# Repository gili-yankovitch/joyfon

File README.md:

# Joyfon

A USB HID game controller for the Raspberry Pi Pico (RP2040).

Joyfon enumerates as a **standard USB HID gamepad**, so phones (Android), PCs,
and emulators recognize it with no driver or app. The button layout mimics a
Game Boy Color: a 4-way D-pad plus `A`, `B`, `X`, `Y`, shoulder buttons
(`SR`/`SL`), and `START` / `SELECT`.

## Enclosure & PCB

The 3D-printable enclosure is modeled in Onshape:
[Joyfon case (Onshape)](https://cad.onshape.com/documents/5b058211584da6ba94a5f3a2/w/7946df008143afeea2af8019/e/bb1aadbdb91d94f271c1447f?page=2&email=giliy%40nyxsecurity.net&renderMode=0&uiState=6a5551800e11d12ad61d855e).

| Case front | Case back |
| ---------- | --------- |
|  |  |

| PCB front | PCB back |
| --------- | -------- |
|  |  |

## Wiring

All buttons are **active-low**: wire each button between its GPIO and `GND`.
The firmware enables the RP2040's internal pull-ups, so external pull-up
resistors are optional (the description below assumes you already have them).

| Function        | GPIO  |
| --------------- | ----- |
| D-pad DOWN      | 0     |
| D-pad RIGHT     | 1     |
| D-pad UP        | 2     |
| D-pad LEFT      | 3     |
| B               | 4     |
| A               | 5     |
| X               | 20    |
| Y               | 21    |
| SR (R shoulder) | 22    |
| SL (L shoulder) | 25    |
| START           | 23    |
| SELECT          | 24    |
| Status LED      | 8     |

The status LED (GPIO8, active-high through a current-limiting resistor):

- **Blinks @ 250 ms** — USB not mounted (waiting for host).
- **Blinks @ 1 s** — USB suspended.
- **Solid while pressed** — mounted and running; lights up whenever any button
  is held, as live input feedback.

## HID mapping

The gamepad report is the TinyUSB standard gamepad (`hid_gamepad_report_t`):

| Physical button | HID control                        |
| --------------- | ---------------------------------- |
| D-pad           | Hat switch (8 directions)          |
| A               | Button 1 (`GAMEPAD_BUTTON_A`)      |
| B               | Button 2 (`GAMEPAD_BUTTON_B`)      |
| X               | Button 4 (`GAMEPAD_BUTTON_X`)      |
| Y               | Button 5 (`GAMEPAD_BUTTON_Y`)      |
| SR (R shoulder) | Button 8 (`GAMEPAD_BUTTON_TR`)     |
| SL (L shoulder) | Button 7 (`GAMEPAD_BUTTON_TL`)     |
| START           | Button 12 (`GAMEPAD_BUTTON_START`) |
| SELECT          | Button 11 (`GAMEPAD_BUTTON_SELECT`)|

Opposing D-pad directions cancel out (e.g. pressing UP and DOWN together
reports centered) so no impossible diagonal is ever sent. Reports are only sent
when the button state changes, keeping latency low and the bus quiet.

## Building

This project expects the [pico-sdk](https://github.com/raspberrypi/pico-sdk).
By default `CMakeLists.txt` looks for it at `../pico-sdk` (a sibling of this
folder). You can override that with the `PICO_SDK_PATH` environment variable.

Prerequisites: `cmake` (>= 3.13), the `arm-none-eabi` GCC toolchain, and the
SDK submodules (TinyUSB) initialized.

```bash
# from the joyfon/ directory
mkdir build && cd build
cmake ..                    # or: cmake -DPICO_SDK_PATH=/path/to/pico-sdk ..
make -j
```

The build produces `build/joyfon.uf2`.

## Flashing

1. Hold the **BOOTSEL** button while plugging the Pico into USB; it mounts as a
   mass-storage drive (`RPI-RP2`).
2. Copy `joyfon.uf2` onto it. The Pico reboots and re-enumerates as the
   "Joyfon Game Controller" gamepad.

After flashing, plug the Pico into a phone (via USB-OTG / USB-C). It should
appear as a connected gamepad, ready for use with emulators or any app that
supports HID controllers.

## Notes

- Uses the test VID `0xCafe` / PID `0x4007`. Use a VID/PID you own before
  distributing hardware.
- The RP2040 USB enumeration errata fix (RP2040-E5) is enabled in
  `CMakeLists.txt`; it reserves GPIO15 internally on RP2040 boards.

## Assembly guide

Open [the illustrated assembly guide](assembly.html) for the complete build sequence,
component inventory, fastener assignments and checks. All 35 assembly photos are
included locally in `images/assembly/`. The page shares the home page styling.

The `stl/` directory contains the 16 production STL parts, including the hinge
height extender and the updated USB holder and cover.

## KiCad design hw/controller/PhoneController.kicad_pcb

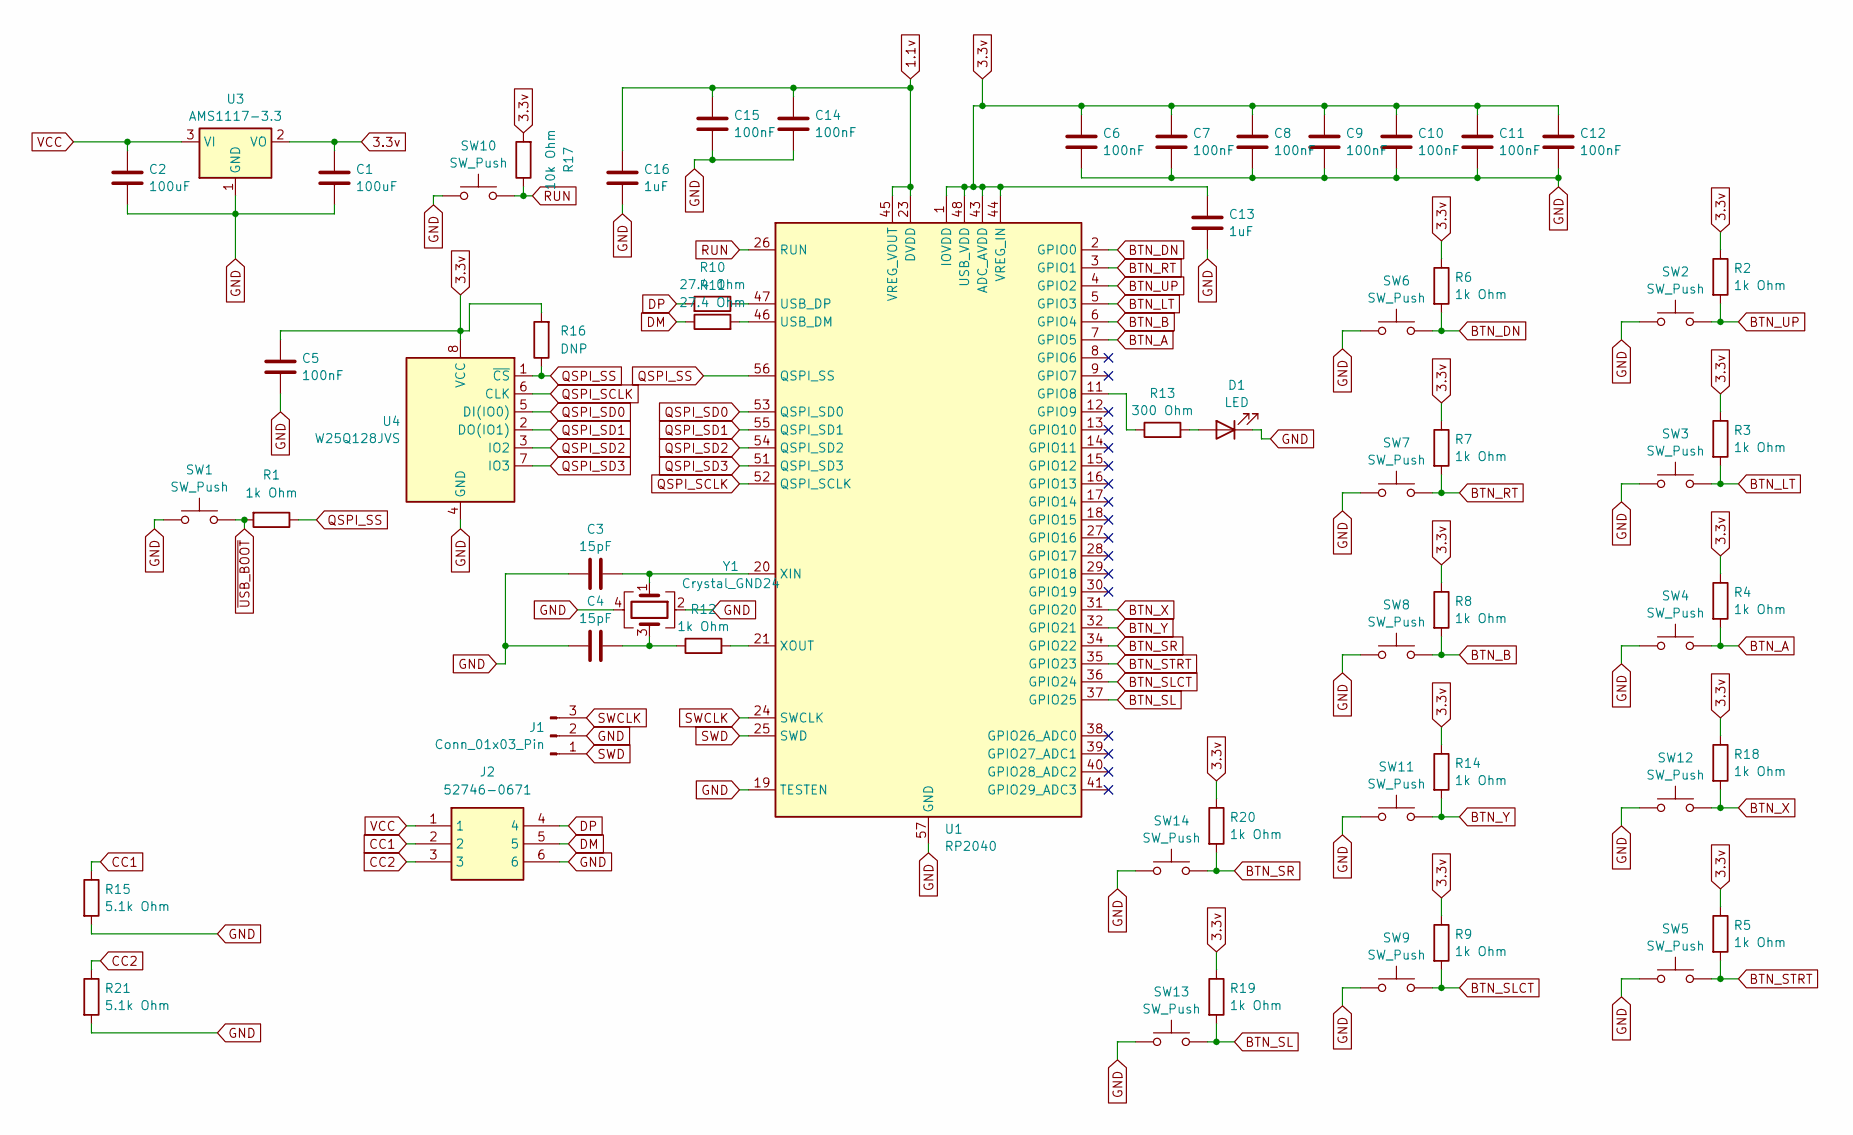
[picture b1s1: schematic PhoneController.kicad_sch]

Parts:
C1, C2: 100uF; C_1206_3216Metric_Pad1.33x1.80mm_HandSolder
C3, C4: 15pF; C_0805_2012Metric_Pad1.18x1.45mm_HandSolder
C5, C6, C7, C8, C9, C10, C11, C12, C14, C15: 100nF; C_0805_2012Metric_Pad1.18x1.45mm_HandSolder
C13, C16: 1uF; C_0805_2012Metric_Pad1.18x1.45mm_HandSolder
D1: LED; LED_0805_2012Metric_Pad1.15x1.40mm_HandSolder
J1: Conn_01x03_Pin; PinSocket_1x03_P2.54mm_Vertical
J2: 52746-0671; Mouser Part Number 538-52746-0671
R1, R2, R3, R4, R5, R6, R7, R8, R9, R12, R14, R18, R19, R20: 1k Ohm; R_0805_2012Metric_Pad1.20x1.40mm_HandSolder
R10, R11: 27.4 Ohm; R_0805_2012Metric_Pad1.20x1.40mm_HandSolder
R13: 300 Ohm; R_0805_2012Metric_Pad1.20x1.40mm_HandSolder
R15, R21: 5.1k Ohm; R_0805_2012Metric_Pad1.20x1.40mm_HandSolder
R16: DNP; R_0805_2012Metric_Pad1.20x1.40mm_HandSolder
R17: 10k Ohm; R_0805_2012Metric_Pad1.20x1.40mm_HandSolder
SW1, SW2, SW3, SW4, SW5, SW6, SW7, SW8, SW9, SW10, SW11, SW12, SW13, SW14: SW_Push; TS-1088-AR02016
U1: RP2040; QFN-56-1EP_7x7mm_P0.4mm_EP3.2x3.2mm
U3: AMS1117-3.3; SOT-223-3_TabPin2
U4: W25Q128JVS; SOIC127P790X216-8N
Y1: Crystal_GND24; Crystal_SMD_Abracon_ABM8G-4Pin_3.2x2.5mm

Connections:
1.1v: C14.2, C15.2, C16.2, U1.23 (DVDD), U1.45 (VREG_VOUT), U1.50 (DVDD)
3.3v: C1.1, C5.2, C6.2, C7.2, C8.2, C9.2, C10.2, C11.2, C12.2, C13.2, R2.1, R3.1, R4.1, R5.1, R6.1, R7.1, R8.1, R9.1, R14.1, R16.2, R17.2, R18.1, R19.1, R20.1, U1.1 (IOVDD), U1.10 (IOVDD), U1.22 (IOVDD), U1.33 (IOVDD), U1.42 (IOVDD), U1.43 (ADC_AVDD), U1.44 (VREG_IN), U1.48 (USB_VDD), U1.49 (IOVDD), U3.2 (VO), U4.8 (VCC)
BTN_A: R4.2, SW4.2, U1.7 (GPIO5)
BTN_B: R8.2, SW8.2, U1.6 (GPIO4)
BTN_DN: R6.2, SW6.2, U1.2 (GPIO0)
BTN_LT: R3.2, SW3.2, U1.5 (GPIO3)
BTN_RT: R7.2, SW7.2, U1.3 (GPIO1)
BTN_SL: R19.2, SW13.2, U1.37 (GPIO25)
BTN_SLCT: R9.2, SW9.2, U1.36 (GPIO24)
BTN_SR: R20.2, SW14.2, U1.34 (GPIO22)
BTN_STRT: R5.2, SW5.2, U1.35 (GPIO23)
BTN_UP: R2.2, SW2.2, U1.4 (GPIO2)
BTN_X: R18.2, SW12.2, U1.31 (GPIO20)
BTN_Y: R14.2, SW11.2, U1.32 (GPIO21)
CC1: J2.2, R15.1
CC2: J2.3, R21.1
DM: J2.5, R11.1
DP: J2.4, R10.2
GND: C1.2, C2.2, C3.1, C4.1, C5.1, C6.1, C7.1, C8.1, C9.1, C10.1, C11.1, C12.1, C13.1, C14.1, C15.1, C16.1, D1.1 (K), J1.2, J2.6, R15.2, R21.2, SW1.1, SW2.1, SW3.1, SW4.1, SW5.1, SW6.1, SW7.1, SW8.1, SW9.1, SW10.1, SW11.1, SW12.1, SW13.1, SW14.1, U1.19 (TESTEN), U1.57 (GND), U3.1 (GND), U4.4 (GND), Y1.2, Y1.4
unnamed: C4.2, R12.1, Y1.3
unnamed: D1.2 (A), R13.2
unnamed: R13.1, U1.11 (GPIO8)
unnamed: R11.2, U1.46 (USB_DM)
unnamed: R10.1, U1.47 (USB_DP)
unnamed: C3.2, U1.20 (XIN), Y1.1
unnamed: R12.2, U1.21 (XOUT)
QSPI_SCLK: U1.52 (QSPI_SCLK), U4.6 (CLK)
QSPI_SD0: U1.53 (QSPI_SD0), U4.5 (DI(IO0))
QSPI_SD1: U1.55 (QSPI_SD1), U4.2 (DO(IO1))
QSPI_SD2: U1.54 (QSPI_SD2), U4.3 (IO2)
QSPI_SD3: U1.51 (QSPI_SD3), U4.7 (IO3)
QSPI_SS: R1.1, R16.1, U1.56 (QSPI_SS), U4.1 (~CS)
RUN: R17.1, SW10.2, U1.26 (RUN)
SWCLK: J1.3, U1.24 (SWCLK)
SWD: J1.1, U1.25 (SWD)
VCC: C2.1, J2.1, U3.3 (VI)
~USB_BOOT: R1.2, SW1.2

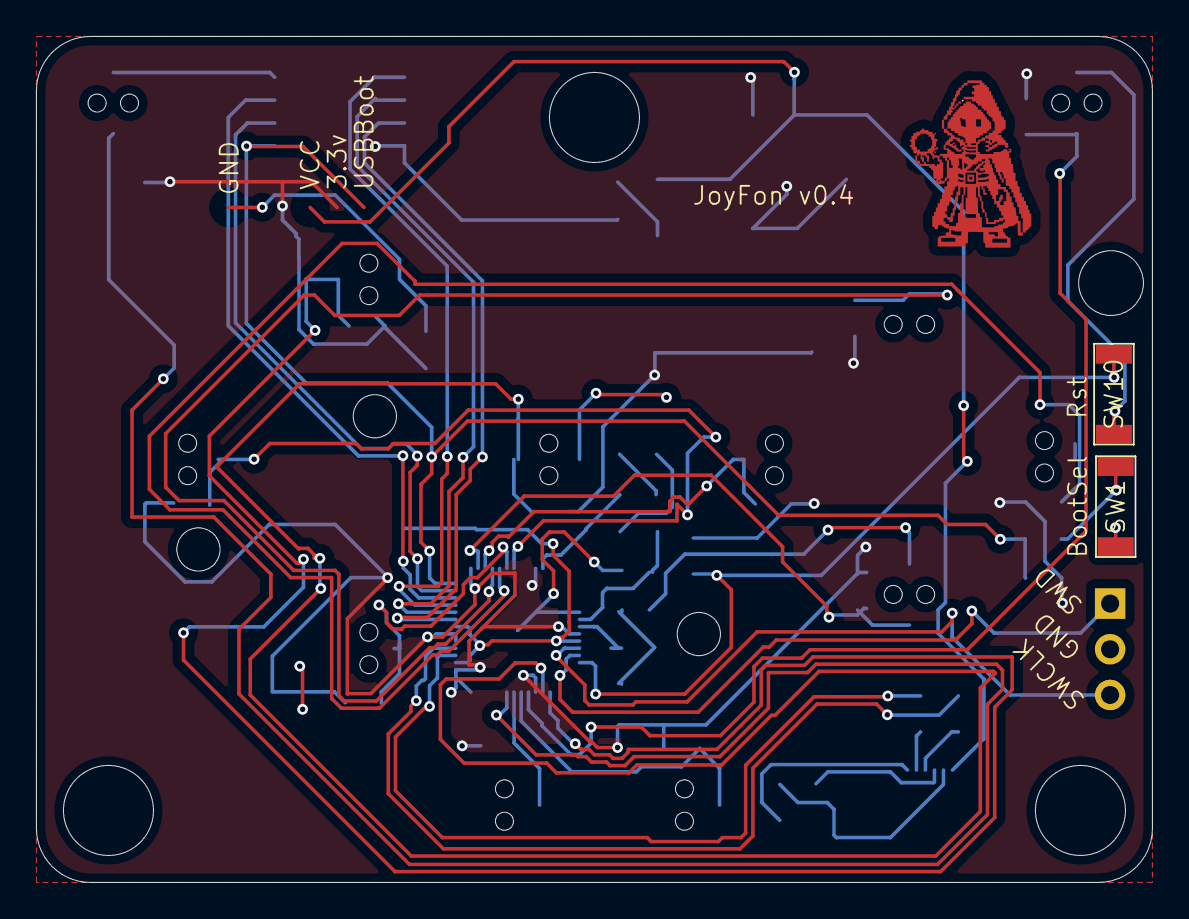
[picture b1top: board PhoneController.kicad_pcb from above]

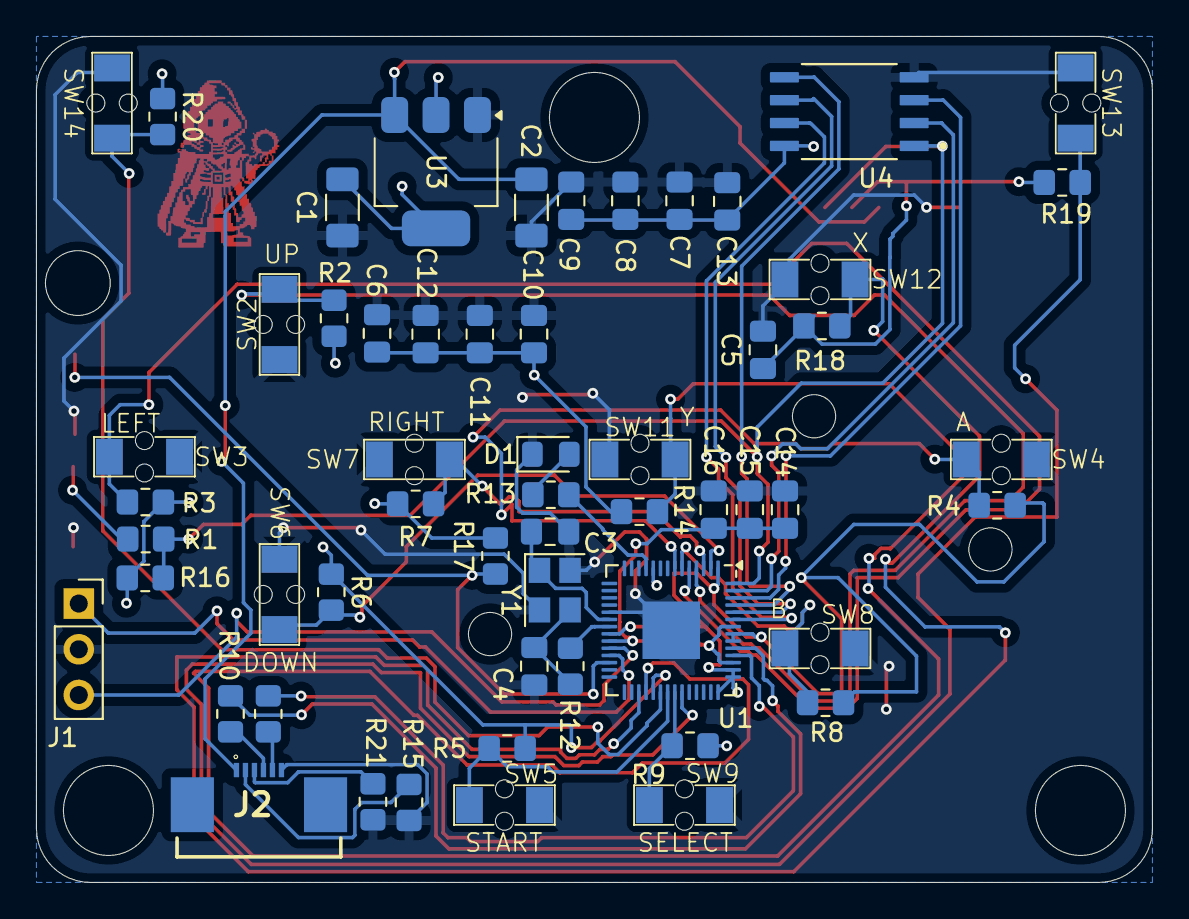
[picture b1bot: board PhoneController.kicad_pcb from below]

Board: 2 copper layers, 62.0 x 47.0 mm, 58 parts (56 on the bottom side), 37 nets.

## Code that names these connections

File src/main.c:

/*
 * Joyfon - a USB HID game controller for the Raspberry Pi Pico.
 *
 * Mimics a Game Boy Color button layout (D-pad + A/B + START/SELECT) and
 * presents itself to a host as a wired DualShock 4.
 *
 * A generic HID gamepad works on Android, PC and Linux but is invisible on
 * iOS/iPadOS: Apple's GameController framework only attaches to controllers
 * it recognises by USB VID/PID. Speaking the DualShock 4's identity and
 * input report gets an iPhone to bind a real controller profile, and the
 * same descriptor is understood everywhere else too.
 *
 * Wiring (all buttons are active-low, i.e. wired to GND, using the internal
 * pull-ups - external pull-ups are also fine):
 *
 *   GPIO0  -> D-pad DOWN
 *   GPIO1  -> D-pad RIGHT
 *   GPIO2  -> D-pad UP
 *   GPIO3  -> D-pad LEFT
 *   GPIO4  -> B
 *   GPIO5  -> A
 *   GPIO20 -> X
 *   GPIO21 -> Y
 *   GPIO22 -> SR (right shoulder)
 *   GPIO25 -> SL (left shoulder)
 *   GPIO23 -> START
 *   GPIO24 -> SELECT
 *   GPIO8  -> status LED (active-high)
 */

#include <string.h>

#include "pico/stdlib.h"
#include "tusb.h"

#include "usb_descriptors.h"
#include "ds4.h"

//--------------------------------------------------------------------+
// Pin configuration
//--------------------------------------------------------------------+

#define PIN_DOWN    0u
#define PIN_RIGHT   1u
#define PIN_UP      2u
#define PIN_LEFT    3u
#define PIN_B       4u
#define PIN_A       5u
#define PIN_X       20u
#define PIN_Y       21u
#define PIN_SR      22u
#define PIN_SL      25u
#define PIN_START   23u
#define PIN_SELECT  24u

#define PIN_LED     8u

// All face/dpad buttons used by the controller, so we can init them in a loop.
static const uint8_t k_button_pins[] = {
  PIN_DOWN, PIN_RIGHT, PIN_UP, PIN_LEFT,
  PIN_B, PIN_A, PIN_X, PIN_Y, PIN_SR, PIN_SL, PIN_START, PIN_SELECT,
};

// Buttons are active-low (pressed == logic 0 thanks to the pull-up).
static inline bool button_pressed(uint8_t pin)
{
  return !gpio_get(pin);
}

//--------------------------------------------------------------------+
// Status LED
//--------------------------------------------------------------------+

// Blink intervals (ms) signalling the USB connection state.
enum {
  BLINK_NOT_MOUNTED = 250,
  BLINK_SUSPENDED   = 1000,
};

// 0 means "don't blink, let the application drive the LED directly".
static uint32_t blink_interval_ms = BLINK_NOT_MOUNTED;

static inline uint32_t now_ms(void)
{
  return to_ms_since_boot(get_absolute_time());
}

static void board_setup(void)
{
  for ( size_t i = 0; i < sizeof(k_button_pins) / sizeof(k_button_pins[0]); i++ )
  {
    uint8_t pin = k_button_pins[i];
    gpio_init(pin);
    gpio_set_dir(pin, GPIO_IN);
    // gpio_pull_up(pin);
  }

  gpio_init(PIN_LED);
  gpio_set_dir(PIN_LED, GPIO_OUT);
  gpio_put(PIN_LED, 0);
}

//--------------------------------------------------------------------+
// USB device callbacks
//--------------------------------------------------------------------+

void tud_mount_cb(void)
{
  blink_interval_ms = 0; // application now controls the LED
}

void tud_umount_cb(void)
{
  blink_interval_ms = BLINK_NOT_MOUNTED;
}

void tud_suspend_cb(bool remote_wakeup_en)
{
  (void) remote_wakeup_en;
  blink_interval_ms = BLINK_SUSPENDED;
}

void tud_resume_cb(void)
{
  blink_interval_ms = tud_mounted() ? 0 : BLINK_NOT_MOUNTED;
}

//--------------------------------------------------------------------+
// DualShock 4 input report
//--------------------------------------------------------------------+

static uint8_t compute_hat(bool up, bool down, bool left, bool right)
{
  // Opposite directions cancel out so we never report an impossible diagonal.
  if (up && down)    { up = down = false; }
  if (left && right) { left = right = false; }

  if (up && right)   return DS4_HAT_NE;
  if (up && left)    return DS4_HAT_NW;
  if (down && right) return DS4_HAT_SE;
  if (down && left)  return DS4_HAT_SW;
  if (up)            return DS4_HAT_N;
  if (down)          return DS4_HAT_S;
  if (left)          return DS4_HAT_W;
  if (right)         return DS4_HAT_E;
  return DS4_HAT_NONE;
}

static void build_report(ds4_input_report_t *report, uint8_t counter, uint16_t timestamp)
{
  memset(report, 0, sizeof(*report));

  // No analog sticks on this board: report both centred and both triggers released.
  report->lx = report->ly = DS4_STICK_CENTER;
  report->rx = report->ry = DS4_STICK_CENTER;

  report->buttons0 = compute_hat(
      button_pressed(PIN_UP),
      button_pressed(PIN_DOWN),
      button_pressed(PIN_LEFT),
      button_pressed(PIN_RIGHT));

  // Nintendo face layout on the DualShock diamond: A/B and X/Y swapped from
  // the Sony positions so A sits where Circle is and X where Triangle is.
  if (button_pressed(PIN_A))      report->buttons0 |= DS4_BTN_CIRCLE;
  if (button_pressed(PIN_B))      report->buttons0 |= DS4_BTN_CROSS;
  if (button_pressed(PIN_X))      report->buttons0 |= DS4_BTN_TRIANGLE;
  if (button_pressed(PIN_Y))      report->buttons0 |= DS4_BTN_SQUARE;

  if (button_pressed(PIN_SL))     report->buttons1 |= DS4_BTN_R1;
  if (button_pressed(PIN_SR))     report->buttons1 |= DS4_BTN_L1;
  if (button_pressed(PIN_START))  report->buttons1 |= DS4_BTN_SHARE;
  if (button_pressed(PIN_SELECT)) report->buttons1 |= DS4_BTN_OPTIONS;

  // The low two bits of buttons2 are PS and touchpad-click; the counter lives
  // in the upper six and must advance on every report.
  report->buttons2 = (uint8_t) (counter << 2);

  report->timestamp   = timestamp;
  report->status      = DS4_STATUS_FULL;
  report->touch_count = 0;
}

// Poll buttons and stream a report to the host. Unlike a generic HID gamepad
// we send on every interval rather than only on change: the real controller
// streams continuously, and the report counter has to keep moving for drivers
// that use it to detect a stalled device.
static void hid_task(void)
{
  const uint32_t poll_interval_ms = 5;
  static uint32_t last_poll_ms = 0;
  static uint8_t counter = 0;
  static uint16_t timestamp = 0;

  if ( now_ms() - last_poll_ms < poll_interval_ms ) return;
  last_poll_ms = now_ms();

  ds4_input_report_t report;
  build_report(&report, counter, timestamp);

  // Wake the host if we are suspended and the user presses something.
  if ( tud_suspended() )
  {
    if ( (report.buttons0 & 0xF0) || report.buttons1 ||
         (report.buttons0 & 0x0F) != DS4_HAT_NONE )
    {
      tud_remote_wakeup();
    }
    return;
  }

  if ( !tud_hid_ready() ) return;

  if ( tud_hid_report(DS4_REPORT_ID_INPUT, &report, sizeof(report)) )
  {
    counter = (uint8_t) ((counter + 1) & 0x3F);
    // 5.33 us ticks, so a 5 ms interval advances the stamp by ~938.
    timestamp = (uint16_t) (timestamp + 938);
  }
}

//--------------------------------------------------------------------+
// LED feedback
//--------------------------------------------------------------------+

static void led_task(void)
{
  // When mounted (blink_interval_ms == 0) light the LED while any input is
  // active, giving immediate tactile feedback. Otherwise blink to signal the
  // current USB state.
  if ( blink_interval_ms == 0 )
  {
    bool any = false;

    for ( size_t i = 0; i < sizeof(k_button_pins) / sizeof(k_button_pins[0]); i++ )
    {
      if ( button_pressed(k_button_pins[i]) ) { /* any = true; */  break; }
    }

    gpio_put(PIN_LED, any);
    return;
  }

  static uint32_t last_toggle_ms = 0;
  static bool led_on = false;

  if ( now_ms() - last_toggle_ms < blink_interval_ms ) return;
  last_toggle_ms = now_ms();

  led_on = !led_on;
  gpio_put(PIN_LED, led_on);
}

//--------------------------------------------------------------------+
// Main
//--------------------------------------------------------------------+

int main(void)
{
  board_setup();

  tud_init(BOARD_TUD_RHPORT);

  while (1)
  {
    tud_task();   // service the USB device stack
    hid_task();   // read buttons and send reports
    led_task();   // status / activity LED
  }
}
